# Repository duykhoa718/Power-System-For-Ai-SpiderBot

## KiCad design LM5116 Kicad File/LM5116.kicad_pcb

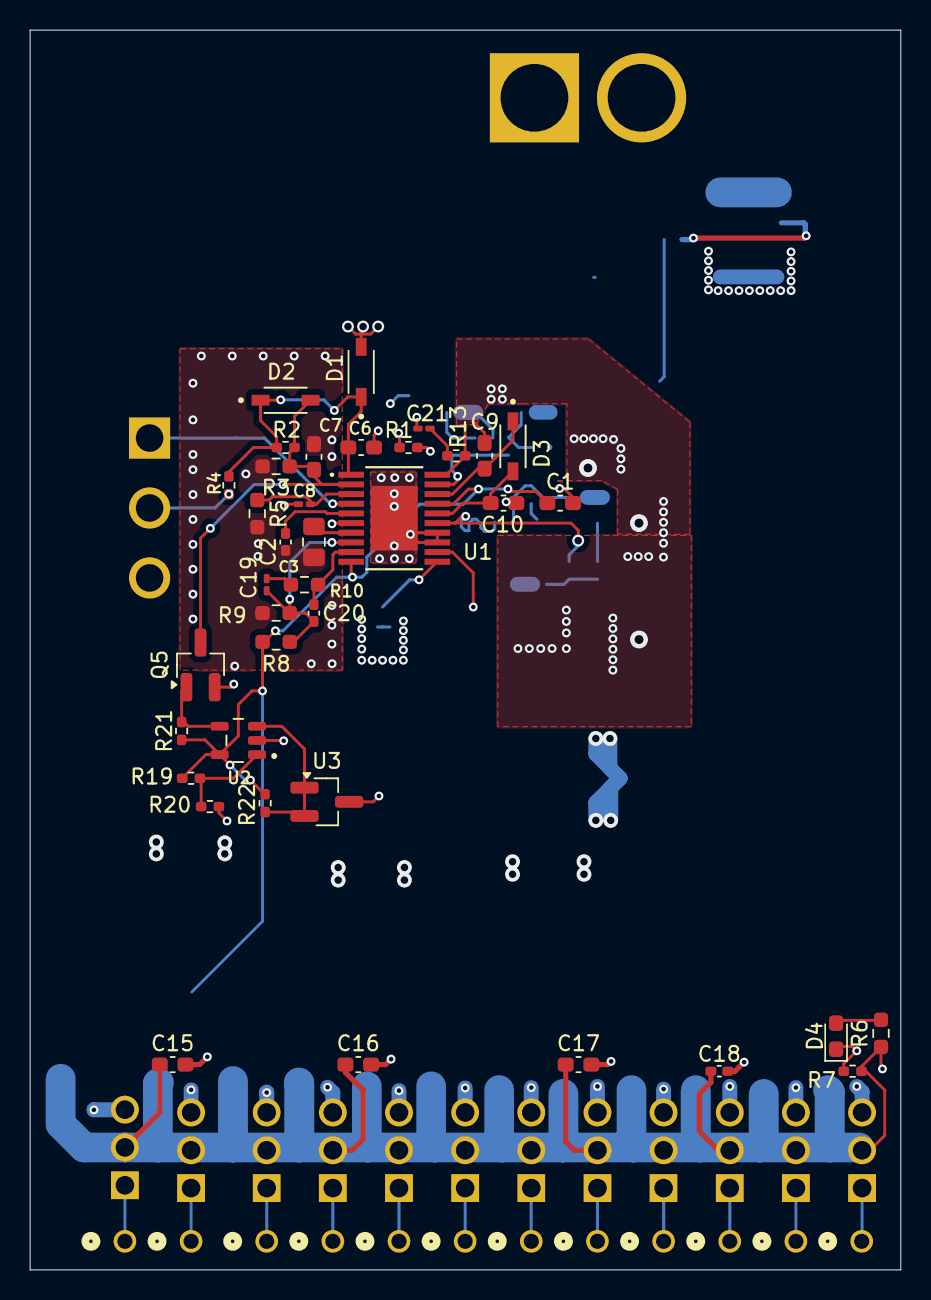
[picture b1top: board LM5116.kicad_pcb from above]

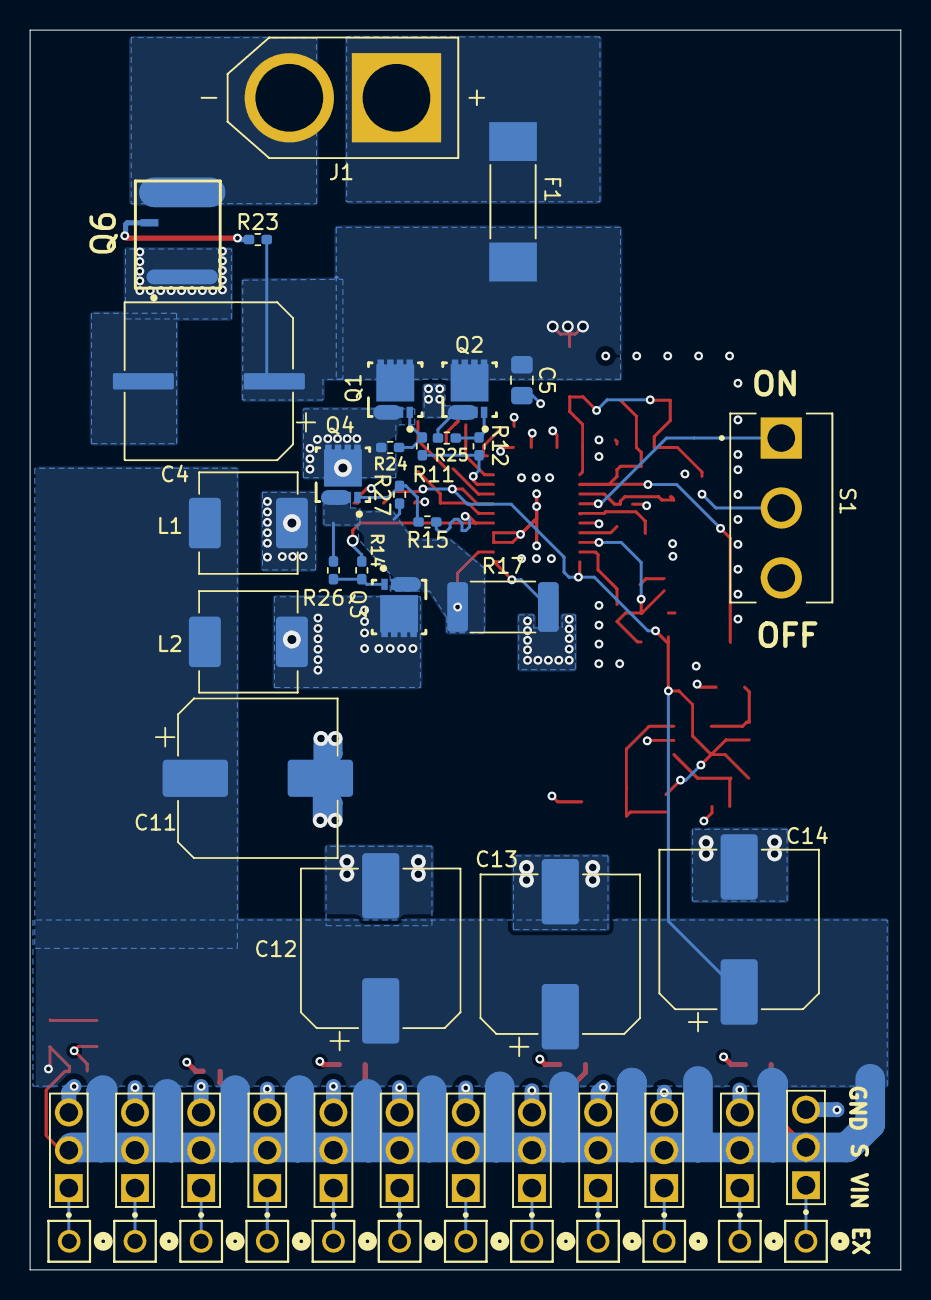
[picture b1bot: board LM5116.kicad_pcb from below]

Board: 4 copper layers, 58.5 x 83.3 mm, 88 parts (50 on the bottom side), 44 nets.

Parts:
C1, C6, C7, C10, C15: 1u; C_0603_1608Metric_Pad1.08x0.95mm_HandSolder
C2: 180p; C_0402_1005Metric_Pad0.74x0.62mm_HandSolder
C3: 33n; C_0805_2012Metric_Pad1.18x1.45mm_HandSolder
C4: 680u; CP_Elec_10x10.5
C5: 4.7u; C_0805_2012Metric_Pad1.18x1.45mm_HandSolder
C8, C19, C21: 100p; C_0201_0603Metric_Pad0.64x0.40mm_HandSolder
C9, C17: 820n; C_0603_1608Metric_Pad1.08x0.95mm_HandSolder
C11, C12, C13, C14: 150u; CP_Elec_10x10.5
C16: 2.2u; C_0603_1608Metric_Pad1.08x0.95mm_HandSolder
C18: 100n; C_0402_1005Metric_Pad0.74x0.62mm_HandSolder
C20: 10p; C_0402_1005Metric_Pad0.74x0.62mm_HandSolder
D1, D2, D3: 1N5819HW-7-F; SOD3715X145N
D4: LED; LED_0603_1608Metric_Pad1.05x0.95mm_HandSolder
F1: 0678H9300-02; FUSC9830X318N
J1: XT60-M; AMASS_XT60-M
J2, J3, J4, J5, J6, J7, J8, J9, J10, J11, J12, J13: PH1-01-UA; CONN_PH1-01-UA_ADM
J14, J15, J16, J17, J18, J19, J20, J21, J22, J23, J24, J25: 61300311121; WURTH_61300311121
L1, L2: 1.38u; L_Pulse_PA4341
Q1, Q2, Q3, Q4: CSD17304Q3; DQG0008A
Q5: 2N7002; SOT-23_Handsoldering
Q6: IQDH29NE2LM5CG; IFX-PG-TTFN-9-2-V
R1: 0; R_0402_1005Metric_Pad0.72x0.64mm_HandSolder
R2: 22.6k; R_0402_1005Metric_Pad0.72x0.64mm_HandSolder
R3: 2.49k; R_0603_1608Metric_Pad0.98x0.95mm_HandSolder
R4: 1Meg; R_0402_1005Metric_Pad0.72x0.64mm_HandSolder
R5: 5.3k; R_0603_1608Metric_Pad0.98x0.95mm_HandSolder
R6: 140; R_0603_1608Metric_Pad0.98x0.95mm_HandSolder
R7: 2k; R_0402_1005Metric_Pad0.72x0.64mm_HandSolder
R8: 5.6k; R_0603_1608Metric_Pad0.98x0.95mm_HandSolder
R9: 1.21k; R_0603_1608Metric_Pad0.98x0.95mm_HandSolder
R10: 226k; R_0603_1608Metric_Pad0.98x0.95mm_HandSolder
R11, R12, R14, R15: 3; R_0402_1005Metric_Pad0.72x0.64mm_HandSolder
R13, R22: 5.83k; R_0402_1005Metric_Pad0.72x0.64mm_HandSolder
R17: 3m; R_2512_6332Metric_Pad1.40x3.35mm_HandSolder
R19, R21, R23, R24, R25, R26, R27: 10k; R_0402_1005Metric_Pad0.72x0.64mm_HandSolder
R20: 4.81k; R_0402_1005Metric_Pad0.72x0.64mm_HandSolder
S1: 100SP1T1B4M2QE; SW_100SP1T1B4M2QE
U1: LM25116MHX/NOPB; MXA20A_TEX-M
U2: TLV1701AIDBVR; SOT95P280X145-5N
U3: TL431DBZ; SOT-23_Handsoldering

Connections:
/1: J2.1 (1_1), J14.1
/2: J3.1 (1_1), J15.1
/3: J4.1 (1_1), J16.1
/4: J5.1 (1_1), J17.1
/5: J6.1 (1_1), J18.1
/6: J7.1 (1_1), J19.1
/7: J8.1 (1_1), J25.1
/8: J9.1 (1_1), J24.1
/9: J10.1 (1_1), J23.1
/10: J11.1 (1_1), J22.1
/11: J12.1 (1_1), J21.1
/12: J13.1 (1_1), J20.1
/COMP: C20.2, R10.2, U1.9 (COMP)
/CS: Q3.1 (Source), Q3.2, Q3.3, Q4.1 (Source), Q4.2, Q4.3, R17.2, R26.1, R27.1, U1.12 (CS)
/EN: S1.1, U1.4 (EN)
/FB: C19.1, C20.1, R8.2, R9.1, U1.8 (FB)
/HB: C9.1, D3.C, U1.18 (HB)
/HO: R11.1, R12.2, U1.19 (HO)
/LO: R14.1, R15.1, U1.15 (LO)
/RT_SYNC: C8.1, R5.1, U1.3 (RT/SYNC)
/SOURCE: C4.1, C5.1, D1.A, F1.2, Q1.5 (Drain), Q1.6, Q1.7, Q1.8, Q1.9, Q2.5 (Drain), Q2.6, Q2.7, Q2.8, Q2.9, R23.2
/SW: C9.2, L1.1, L2.1, Q1.1 (Source), Q1.2, Q1.3, Q2.1 (Source), Q2.2, Q2.3, Q3.5 (Drain), Q3.6, Q3.7, Q3.8, Q3.9, Q4.5 (Drain), Q4.6, Q4.7, Q4.8, Q4.9, R13.1, R24.1, R25.1, U1.20 (SW)
/UVLO: C7.1, D2.A, Q5.3 (D), R2.2, R3.1, U1.2 (ULVO)
/VCC: C10.1, D3.A, U1.16 (VCC)
/VIN: C6.1, D1.C, D2.C, R2.1, R4.1, U1.1 (VIN)
/VOUT: C1.1, C11.1, C12.1, C13.1, C14.1, C15.1, C16.1, C17.1, C18.1, J14.2, J15.2, J16.2, J17.2, J18.2, J19.2, J20.2, J21.2, J22.2, J23.2, J24.2, J25.2, L1.2, L2.2, R6.1, R7.1, R8.1, R19.1, R21.1, R22.1, U1.10 (VOUT), U1.17 (VCCX), U2.5 (V+)
/VREF: R22.2, U2.3 (IN-), U3.1 (K), U3.2 (REF)
GND: C1.2, C2.2, C3.2, C6.2, C7.2, C8.2, C10.2, C21.2, Q5.2 (S), R1.2, R3.2, R5.2, R9.2, R20.2, U1.6 (AGND), U3.3 (A)
GNDPWR: C4.2, C5.2, C11.2, C12.2, C13.2, C14.2, C15.2, C16.2, C17.2, C18.2, D4.1 (K), J14.3, J15.3, J16.3, J17.3, J18.3, J19.3, J20.3, J21.3, J22.3, J23.3, J24.3, J25.3, Q6.1 (SOURCE1), Q6.2 (SOURCE2), Q6.3 (SOURCE3), Q6.4 (SOURCE4), R1.1, R7.2, R17.1, U1.11 (DEMB), U1.13 (CSG), U1.14 (PGND), U1.21 (EP), U2.2 (V-)
unnamed: C19.2, R10.1
unnamed: C21.1, R13.2
unnamed: D4.2 (A), R6.2
unnamed: J1.N (NEG), Q6.5 (DRAIN1), Q6.6 (DRAIN2), Q6.7 (DRAIN3), Q6.8 (DRAIN4)
unnamed: F1.1, J1.P (POS)
unnamed: Q1.4 (Gate), R11.2, R24.2
unnamed: Q2.4 (Gate), R12.1, R25.2
unnamed: Q3.4 (Gate), R14.2, R26.2
unnamed: Q4.4 (Gate), R15.2, R27.2
unnamed: Q5.1 (G), R21.2, U2.4 (OUT)
unnamed: Q6.9 (GATE), R23.1
unnamed: R4.2, S1.2
unnamed: C2.1, U1.5 (RAMP)
unnamed: C3.1, U1.7 (SS)
unnamed: R19.2, R20.1, U2.1 (IN+)

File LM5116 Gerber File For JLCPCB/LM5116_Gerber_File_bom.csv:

Designator,Footprint,Quantity,Value,LCSC Part #
"C1, C10, C15, C6, C7",0603,5,1u,
"C11, C12, C13, C14",CP_Elec_10x10.5,4,150u,
C16,0603,1,2.2u,
"C17, C9",0603,2,820n,
C18,0402,1,100n,
"C19, C21, C8",0201,3,100p,
C2,0402,1,180p,
C20,0402,1,10p,
C3,0805,1,33n,
C4,CP_Elec_10x10.5,1,680u,
C5,0805,1,4.7u,
"D1, D2, D3",SOD3715X145N,3,1N5819HW-7-F,
D4,0603,1,LED,
F1,FUSC9830X318N,1,0678H9300-02,
J1,AMASS_XT60-M,1,XT60-M,
"J10, J11, J12, J13, J2, J3, J4, J5, J6, J7, J8, J9",CONN_PH1-01-UA_ADM,12,PH1-01-UA,
"J14, J15, J16, J17, J18, J19, J20, J21, J22, J23, J24, J25",WURTH_61300311121,12,61300311121,
"L1, L2",L_Pulse_PA4341,2,1.38u,
"Q1, Q2, Q3, Q4",DQG0008A,4,CSD17304Q3,
Q5,SOT-23_Handsoldering,1,2N7002,
Q6,IFX-PG-TTFN-9-2-V,1,IQDH29NE2LM5CG,
R1,0402,1,0,
R10,0603,1,226k,
"R11, R12, R14, R15",0402,4,3,
"R13, R22",0402,2,5.83k,
R17,2512,1,3m,
"R19, R21, R23, R24, R25, R26, R27",0402,7,10k,
R2,0402,1,22.6k,
R20,0402,1,4.81k,
R3,0603,1,2.49k,
R4,0402,1,1Meg,
R5,0603,1,5.3k,
R6,0603,1,140,
R7,0402,1,2k,
R8,0603,1,5.6k,
R9,0603,1,1.21k,
S1,SW_100SP1T1B4M2QE,1,100SP1T1B4M2QE,
U1,MXA20A_TEX-M,1,LM25116MHX/NOPB,
U2,SOT95P280X145-5N,1,TLV1701AIDBVR,
U3,SOT-23_Handsoldering,1,TL431DBZ,

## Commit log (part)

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2026-06-22 Add component
2026-06-22 Adjust footprint
2026-06-22 Add Component Schematic File
2026-06-25 Update mosfet
2026-06-26 Add Gerber File
2026-06-26 Add Kicad File
2026-06-26 Update Kicad Position
2026-06-26 Change gerber and add more info
2026-06-26 Add new Capacitor to input
2026-06-26 Update Footprint
2026-06-26 Add Digikey File Purchase List
2026-06-27 New Gerber File
2026-06-27 Add New Gerber File
2026-06-30 Update Gerber File
